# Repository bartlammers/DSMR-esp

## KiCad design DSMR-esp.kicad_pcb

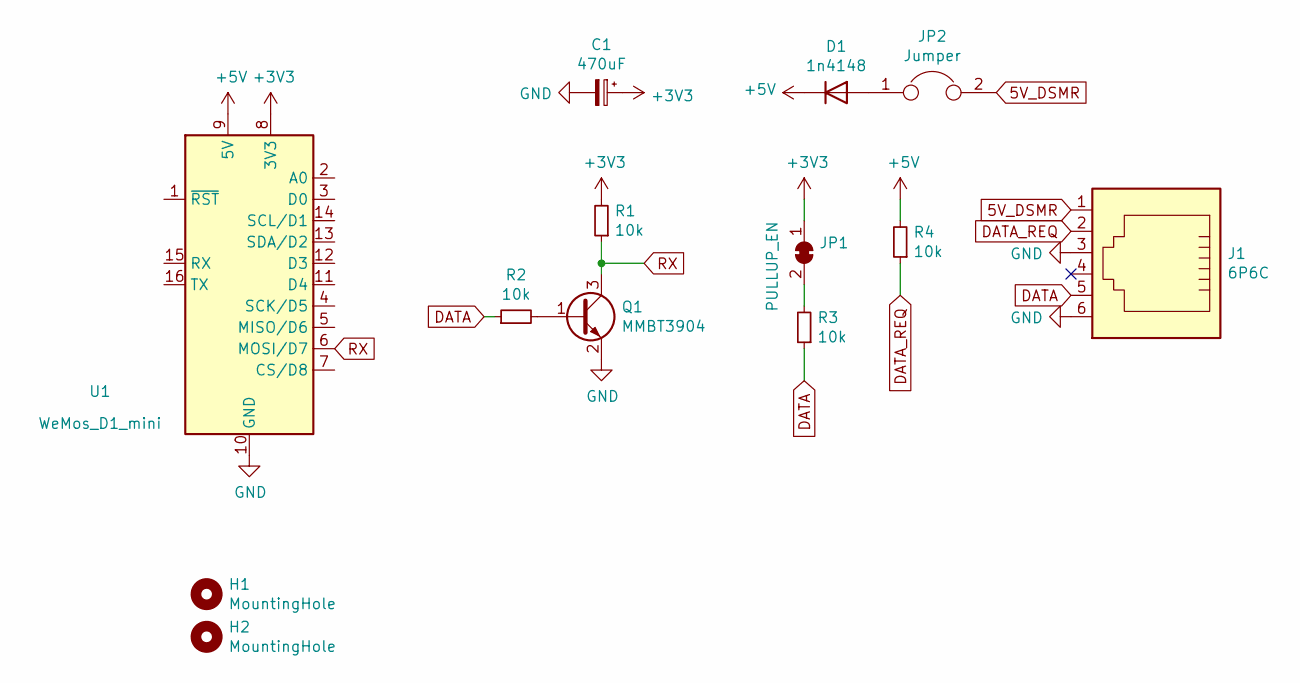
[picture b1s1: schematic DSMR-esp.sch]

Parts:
C1: 470uF; CP_Elec_6.3x7.7
D1: 1n4148; D_SMA_Handsoldering
H1, H2: MountingHole; MountingHole_3.2mm_M3_Pad_Via
J1: 6P6C; RJ12_Amphenol_54601
JP1: PULLUP_EN; SolderJumper-2_P1.3mm_Bridged_RoundedPad1.0x1.5mm
JP2: Jumper; PinHeader_1x02_P2.54mm_Vertical
Q1: MMBT3904; SOT-23_Handsoldering
R1, R2, R3, R4: 10k; R_0805_2012Metric_Pad1.15x1.40mm_HandSolder
U1: WeMos_D1_mini; WEMOS_D1_mini_light

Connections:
5V_DSMR: J1.1, JP2.2
+3V3: C1.1, JP1.1 (A), R1.2, U1.8 (3V3)
+5V: D1.1 (K), R4.2, U1.9 (5V)
DATA: J1.5, R2.1, R3.1
DATA_REQ: J1.2, R4.1
GND: C1.2, J1.3, J1.6, Q1.2 (E), U1.10 (GND)
unnamed: D1.2 (A), JP2.1
unnamed: JP1.2 (B), R3.2
unnamed: Q1.1 (B), R2.2
RX: Q1.3 (C), R1.1, U1.6 (MOSI/D7)

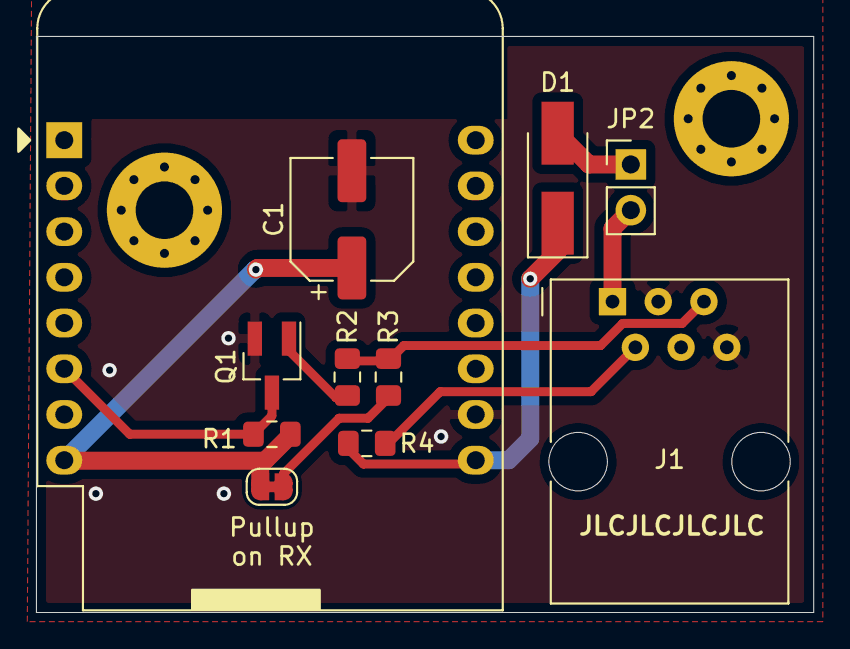
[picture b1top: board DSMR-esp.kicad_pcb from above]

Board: 2 copper layers, 43.2 x 32.0 mm, 13 parts (0 on the bottom side), 10 nets.
